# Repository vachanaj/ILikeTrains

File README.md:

# ILikeTrains

| Item                                                | Your team's answer                                   |
| --------------------------------------------------- | ---------------------------------------------------- |
| Section owners                                      | Introduction: Vachana, Related Work: Mohsen, David: Power supply, Ebba: Transmitter                                                     |
| Who owns main.tex, preamble.tex, macros.tex         | David                                                |
| Who owns the .bib files, or how they are split      | Ebba                                                 |
| Review turnaround expectation                       | e.g. within 24 h on weekdays                         |
| Where PR review requests are announced              | e.g. team Discord/Teams channel                      |
| Merge method                                        | Squash                                               |
| Definition of done for a section                    | e.g. compiles, cited, reviewed, cross-referenced     |

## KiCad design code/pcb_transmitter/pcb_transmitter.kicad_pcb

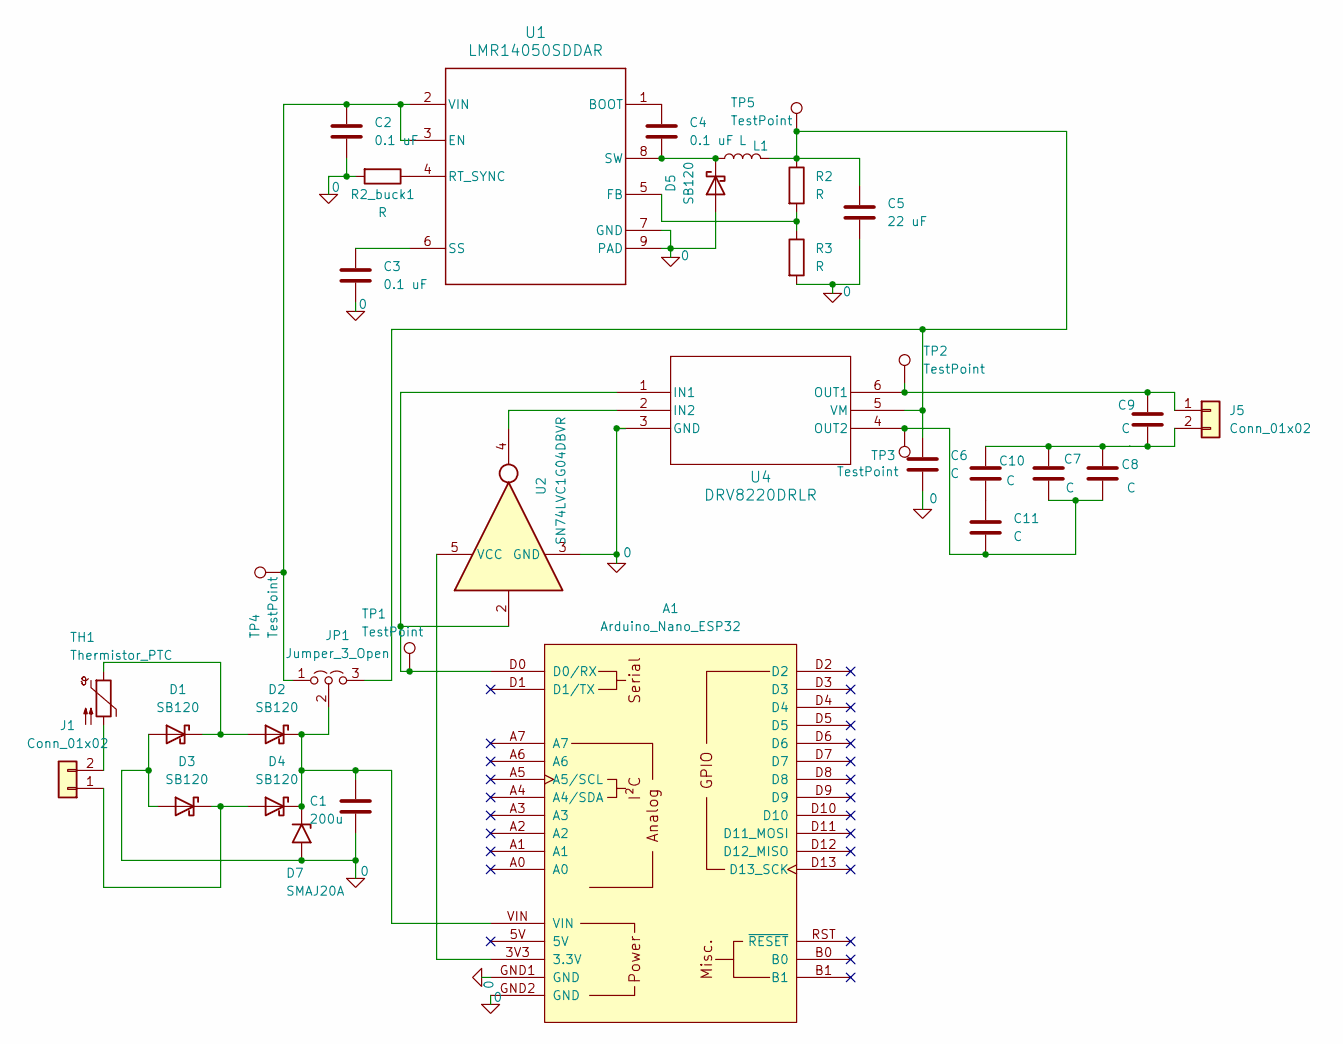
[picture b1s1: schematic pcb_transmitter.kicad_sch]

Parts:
A1: Arduino_Nano_ESP32; Arduino_Nano_ESP32_Socket
C1: 200u; CP_Radial_D8.0mm_P3.50mm
C2, C3, C4: 0.1 uF; C_1210_3225Metric
C5: 22 uF; C_1210_3225Metric
C6: C; C_1210_3225Metric
C7, C8, C9, C10, C11: C; C_Rect_L7.2mm_W5.5mm_P5.00mm_FKS2_FKP2_MKS2_MKP2
D1, D2, D3, D4, D5: SB120; D_SOD-123F
D7: SMAJ20A; D_SMA
J1, J5: Conn_01x02; PinHeader_1x02_P2.54mm_Vertical
JP1: Jumper_3_Open; PinHeader_1x03_P2.54mm_Vertical
L1: L; L_Bourns_SRN6045TA
R2, R2_buck1, R3: R; R_0805_2012Metric
TH1: Thermistor_PTC; Fuse_1812_4532Metric
TP1, TP2, TP3, TP4, TP5: TestPoint; TestPoint_THTPad_1.5x1.5mm_Drill0.8mm
U1: LMR14050SDDAR; SOIC-8-1EP_3.9x4.9mm_P1.27mm_EP2.41x3.3mm_ThermalVias
U2: SN74LVC1G04DBVR; SOT-23-5
U4: DRV8220DRLR; SOT-563

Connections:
0: A1.GND1 (GND), A1.GND2 (GND), C1.2, C2.2, C3.2, C5.2, C6.2, D1.2 (A), D3.2 (A), D5.2 (A), D7.2 (A2), R2_buck1.2, R3.2, U1.7 (GND), U1.9 (PAD), U2.3 (GND), U4.3 (GND)
unnamed: A1.3V3 (3.3V), U2.5 (VCC)
unnamed: A1.D0 (D0/RX), TP1.1 (1_1), U2.2, U4.1 (IN1)
unnamed: C10.2, C11.1
unnamed: D1.1 (K), D2.2 (A), TH1.1
unnamed: A1.VIN, C1.1, D2.1 (K), D4.1 (K), D7.1 (A1), JP1.2 (C)
unnamed: D3.1 (K), D4.2 (A), J1.1
unnamed: C4.2, D5.1 (K), L1.1, U1.8 (SW)
unnamed: J1.2, TH1.2
unnamed: C9.1, J5.1, TP2.1 (1_1), U4.6 (OUT1)
unnamed: C7.1, C8.2, C9.2, C10.1, J5.2
unnamed: C2.1, JP1.1 (A), TP4.1 (1_1), U1.2 (VIN), U1.3 (EN)
unnamed: C5.1, C6.1, JP1.3 (B), L1.2, R2.1, TP5.1 (1_1), U4.5 (VM)
unnamed: C4.1, U1.1 (BOOT)
unnamed: R2.2, R3.1, U1.5 (FB)
unnamed: R2_buck1.1, U1.4 (RT_SYNC)
unnamed: C3.1, U1.6 (SS)
unnamed: U2.4, U4.2 (IN2)
unnamed: C7.2, C8.1, C11.2, TP3.1 (1_1), U4.4 (OUT2)

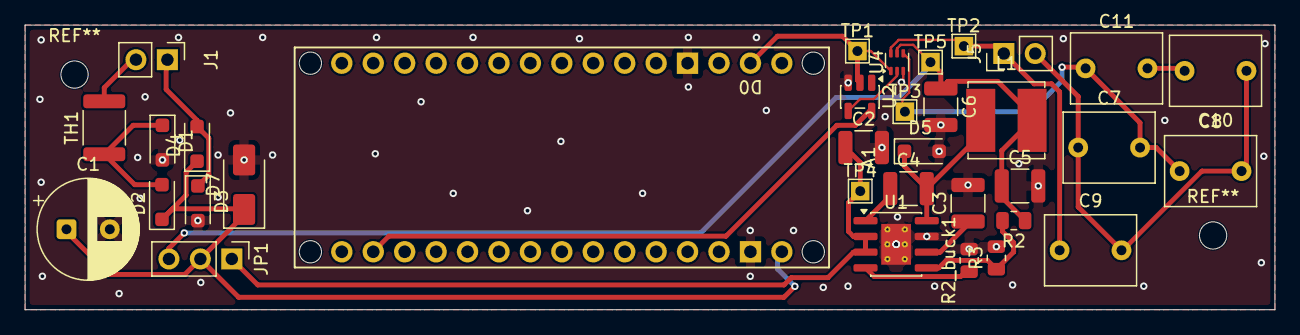
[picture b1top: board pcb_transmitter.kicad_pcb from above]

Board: 2 copper layers, 101.0 x 23.0 mm, 34 parts (0 on the bottom side), 19 nets.
